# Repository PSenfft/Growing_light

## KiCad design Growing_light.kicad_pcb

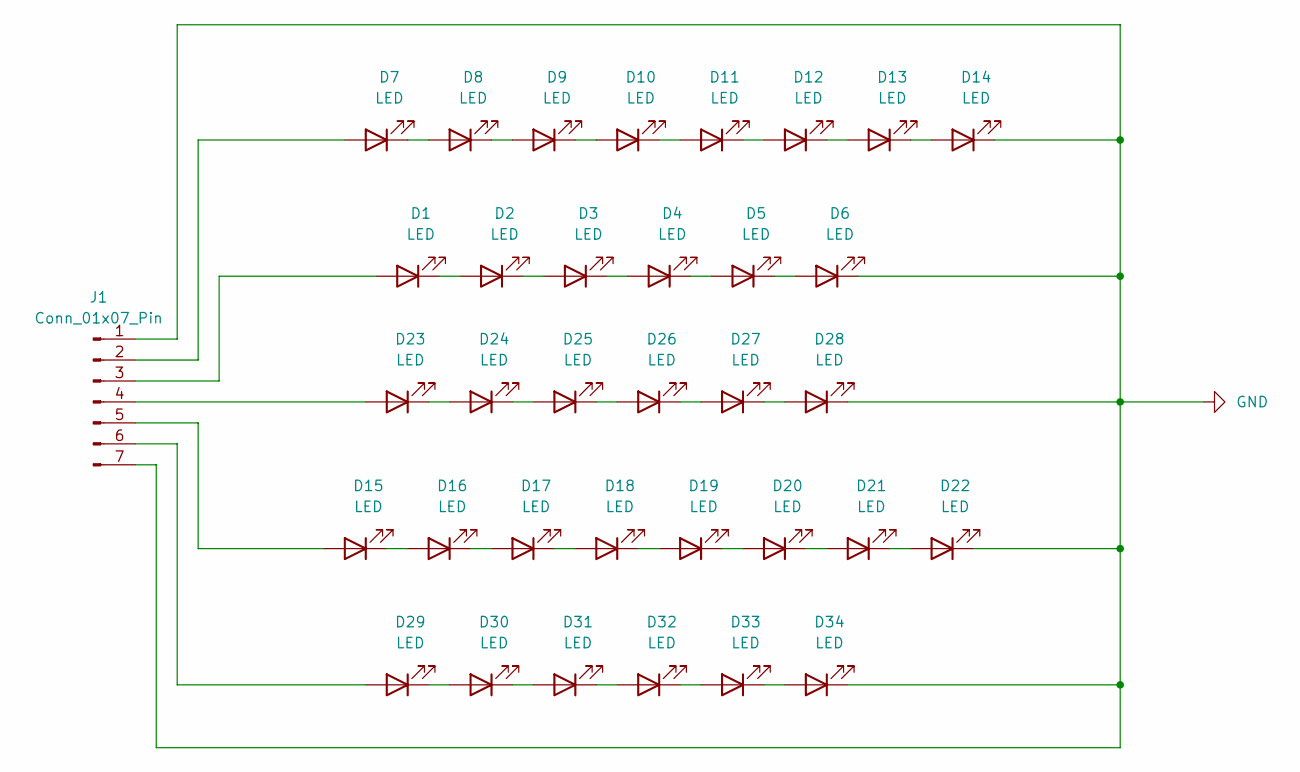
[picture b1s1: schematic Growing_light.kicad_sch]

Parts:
D1, D2, D3, D4, D5, D6, D7, D8, D9, D10, D11, D12, D13, D14, D15, D16, D17, D18, D19, D20, D21, D22, D23, D24, D25, D26, D27, D28, D29, D30, D31, D32, D33, D34: LED; SOB_LED
J1: Conn_01x07_Pin; PinHeader_1x07_P2.54mm_Vertical

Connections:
GND: D6.1 (K), D14.1 (K), D22.1 (K), D28.1 (K), D34.1 (K), J1.1, J1.7
unnamed: D1.2 (A), J1.3
unnamed: D1.1 (K), D2.2 (A)
unnamed: D2.1 (K), D3.2 (A)
unnamed: D3.1 (K), D4.2 (A)
unnamed: D4.1 (K), D5.2 (A)
unnamed: D5.1 (K), D6.2 (A)
unnamed: D7.2 (A), J1.2
unnamed: D7.1 (K), D8.2 (A)
unnamed: D8.1 (K), D9.2 (A)
unnamed: D9.1 (K), D10.2 (A)
unnamed: D10.1 (K), D11.2 (A)
unnamed: D11.1 (K), D12.2 (A)
unnamed: D12.1 (K), D13.2 (A)
unnamed: D13.1 (K), D14.2 (A)
unnamed: D15.2 (A), J1.5
unnamed: D15.1 (K), D16.2 (A)
unnamed: D16.1 (K), D17.2 (A)
unnamed: D17.1 (K), D18.2 (A)
unnamed: D18.1 (K), D19.2 (A)
unnamed: D19.1 (K), D20.2 (A)
unnamed: D20.1 (K), D21.2 (A)
unnamed: D21.1 (K), D22.2 (A)
unnamed: D23.2 (A), J1.4
unnamed: D23.1 (K), D24.2 (A)
unnamed: D24.1 (K), D25.2 (A)
unnamed: D25.1 (K), D26.2 (A)
unnamed: D26.1 (K), D27.2 (A)
unnamed: D27.1 (K), D28.2 (A)
unnamed: D29.2 (A), J1.6
unnamed: D29.1 (K), D30.2 (A)
unnamed: D30.1 (K), D31.2 (A)
unnamed: D31.1 (K), D32.2 (A)
unnamed: D32.1 (K), D33.2 (A)
unnamed: D33.1 (K), D34.2 (A)

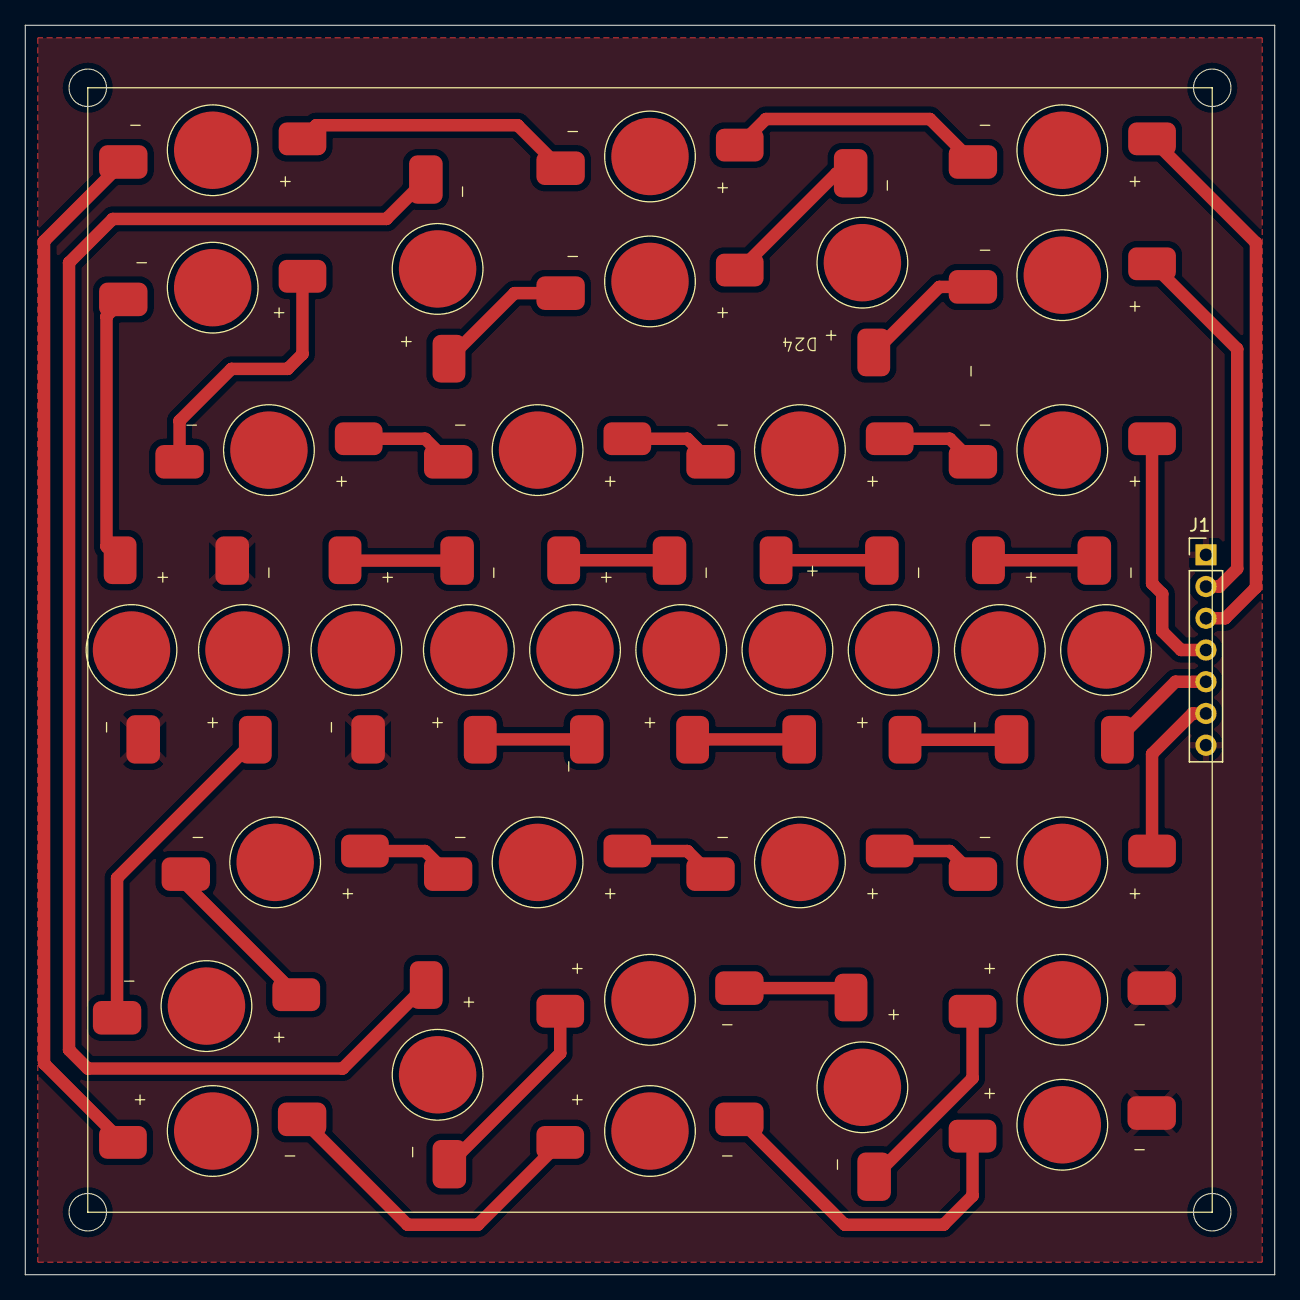
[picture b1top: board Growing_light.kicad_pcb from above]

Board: 2 copper layers, 100.0 x 100.0 mm, 35 parts (0 on the bottom side), 35 nets.

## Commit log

2024-07-24 added files for lioghtng PCB
